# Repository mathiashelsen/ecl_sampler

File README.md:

ecl_sampler
===========

A sampling plugin driven by ECL logic

The idea is that a diode bridge can be pulsed on for a very short time (~50ps) through the use of 
an avalanche transtistor (and possibly step recovery diode.) 

The use of ECL enables a digitally controllable delay line to vary the position of the sample point to the trigger point.

Copyright 2014 by Mathias Helsen, MIT License.

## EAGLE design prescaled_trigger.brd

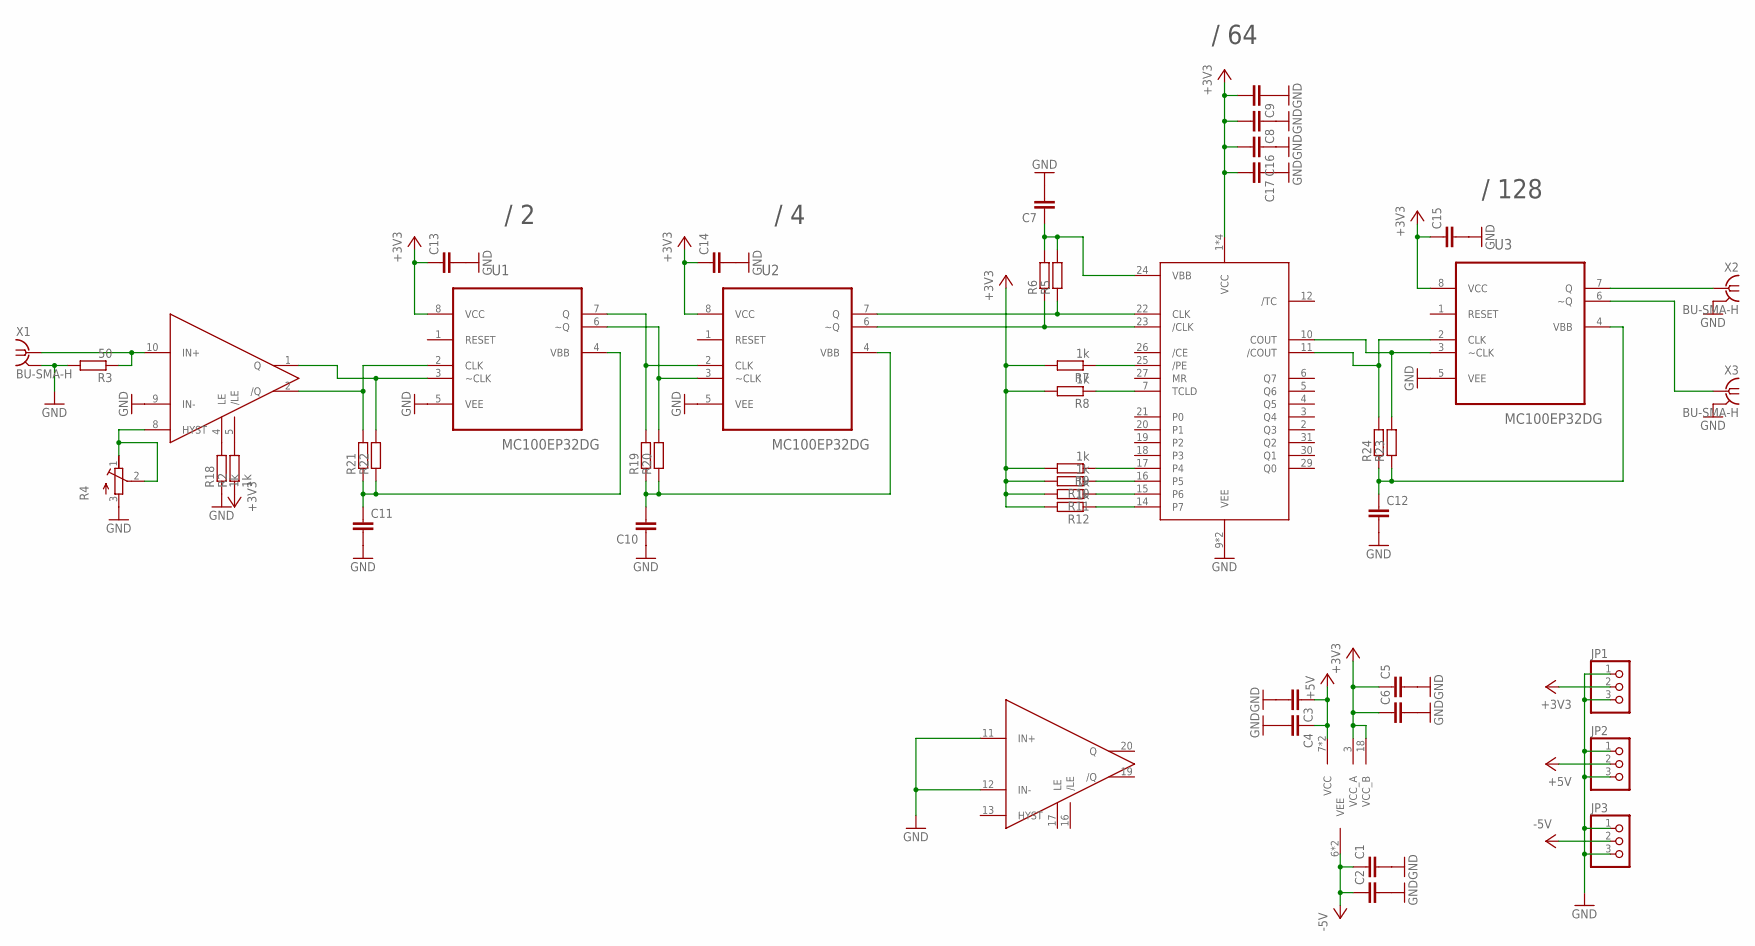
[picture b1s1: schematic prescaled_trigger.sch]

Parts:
C1, C2, C3, C4, C5, C6, C7, C8, C9, C10, C11, C12, C13, C14, C15, C16, C17: C-EUC0805; C0805
JP1, JP2, JP3: PINHD-1X3; 1X03
R2, R7, R8, R9, R10, R11, R12, R18: 1k; M0805
R3: 50; M0805
R4: R-TRIMMT18; RTRIMT18
R5, R6, R19, R20, R21, R22, R23, R24: R-EU_M1206; M1206
U1, U2, U3: MC100EP32DG; SOIC127P600X175-8N
U$1: MAX9601; SSOP20DB
U$2: MC100EP016; QFP80P900X900X160-32N
X1, X2, X3: BU-SMA-H

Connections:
+3V3: C5.1, C6.1, C8.2, C9.2, C13.1, C14.1, C15.1, C16.2, C17.2, JP1.2, R2.1, R7.2, R8.2, R9.2, R10.2, R11.2, R12.2, U1.8 (VCC), U2.8 (VCC), U3.8 (VCC), U$1.3 (VCC_A), U$1.18 (VCC_B), U$2.1 (VCC), U$2.8 (VCC), U$2.13 (VCC), U$2.32 (VCC)
+5V: C3.1, C4.1, JP2.2, U$1.7 (VCC), U$1.14 (VCC)
-5V: C1.1, C2.1, JP3.2, U$1.6 (VEE), U$1.15 (VEE)
/CLKIN: R6.1, U2.6 (~Q), U$2.23 (/CLK)
CLKIN: R5.1, U2.7 (Q), U$2.22 (CLK)
GND: C1.2, C2.2, C3.2, C4.2, C5.2, C6.2, C7.2, C8.1, C9.1, C10.1, C11.2, C12.2, C13.2, C14.2, C15.2, C16.1, C17.1, JP1.1, JP1.3, JP2.1, JP2.3, JP3.1, JP3.3, R3.2, R4.3 (E), R18.1, U1.5 (VEE), U2.5 (VEE), U3.5 (VEE), U$1.9 (IN-), U$1.11 (IN+), U$1.12 (IN-), U$2.9 (VEE), U$2.28 (VEE), X1.2, X1.3 (2), X1.4 (2), X1.5 (2), X2.2, X2.3 (2), X2.4 (2), X2.5 (2), X3.2, X3.3 (2), X3.4 (2), X3.5 (2)
unnamed: R2.2, U$1.5 (/LE)
unnamed: R11.1, U$2.15 (P6)
unnamed: R4.1 (A), R4.2 (S), U$1.8 (HYST)
unnamed: R10.1, U$2.16 (P5)
unnamed: R9.1, U$2.17 (P4)
unnamed: R12.1, U$2.14 (P7)
unnamed: R8.1, U$2.7 (TCLD)
unnamed: R7.1, U$2.25 (/PE)
unnamed: R18.2, U$1.4 (LE)
unnamed: C11.1, R21.1, R22.1, U1.4 (VBB)
unnamed: R21.2, U1.2 (CLK), U$1.2 (/Q)
unnamed: R22.2, U1.3 (~CLK), U$1.1 (Q)
unnamed: C10.2, R19.1, R20.1, U2.4 (VBB)
unnamed: R19.2, U1.7 (Q), U2.2 (CLK)
unnamed: R20.2, U1.6 (~Q), U2.3 (~CLK)
unnamed: U3.7 (Q), X2.1
unnamed: U3.6 (~Q), X3.1
unnamed: C12.1, R23.1, R24.1, U3.4 (VBB)
unnamed: R24.2, U3.2 (CLK), U$2.11 (/COUT)
unnamed: R23.2, U3.3 (~CLK), U$2.10 (COUT)
RFIN: R3.1, U$1.10 (IN+), X1.1
VBB: C7.1, R5.2, R6.2, U$2.24 (VBB)

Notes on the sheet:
/ 2
/ 4
/ 64
/ 128

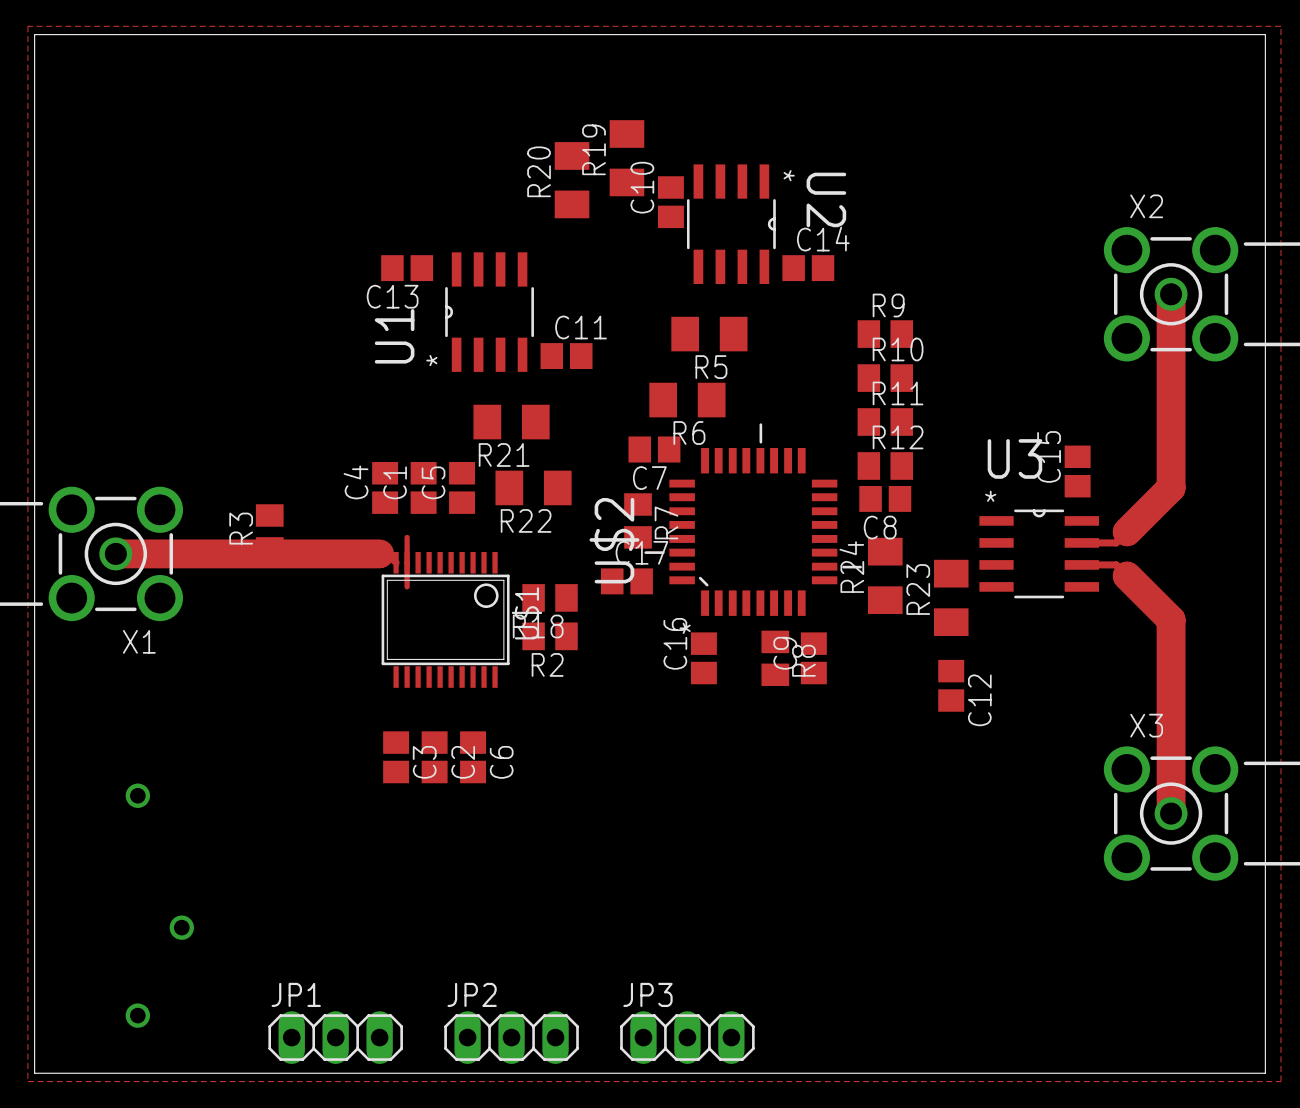
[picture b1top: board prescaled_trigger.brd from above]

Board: 2 copper layers, 71.1 x 60.0 mm, 46 parts (1 on the bottom side), 28 nets.

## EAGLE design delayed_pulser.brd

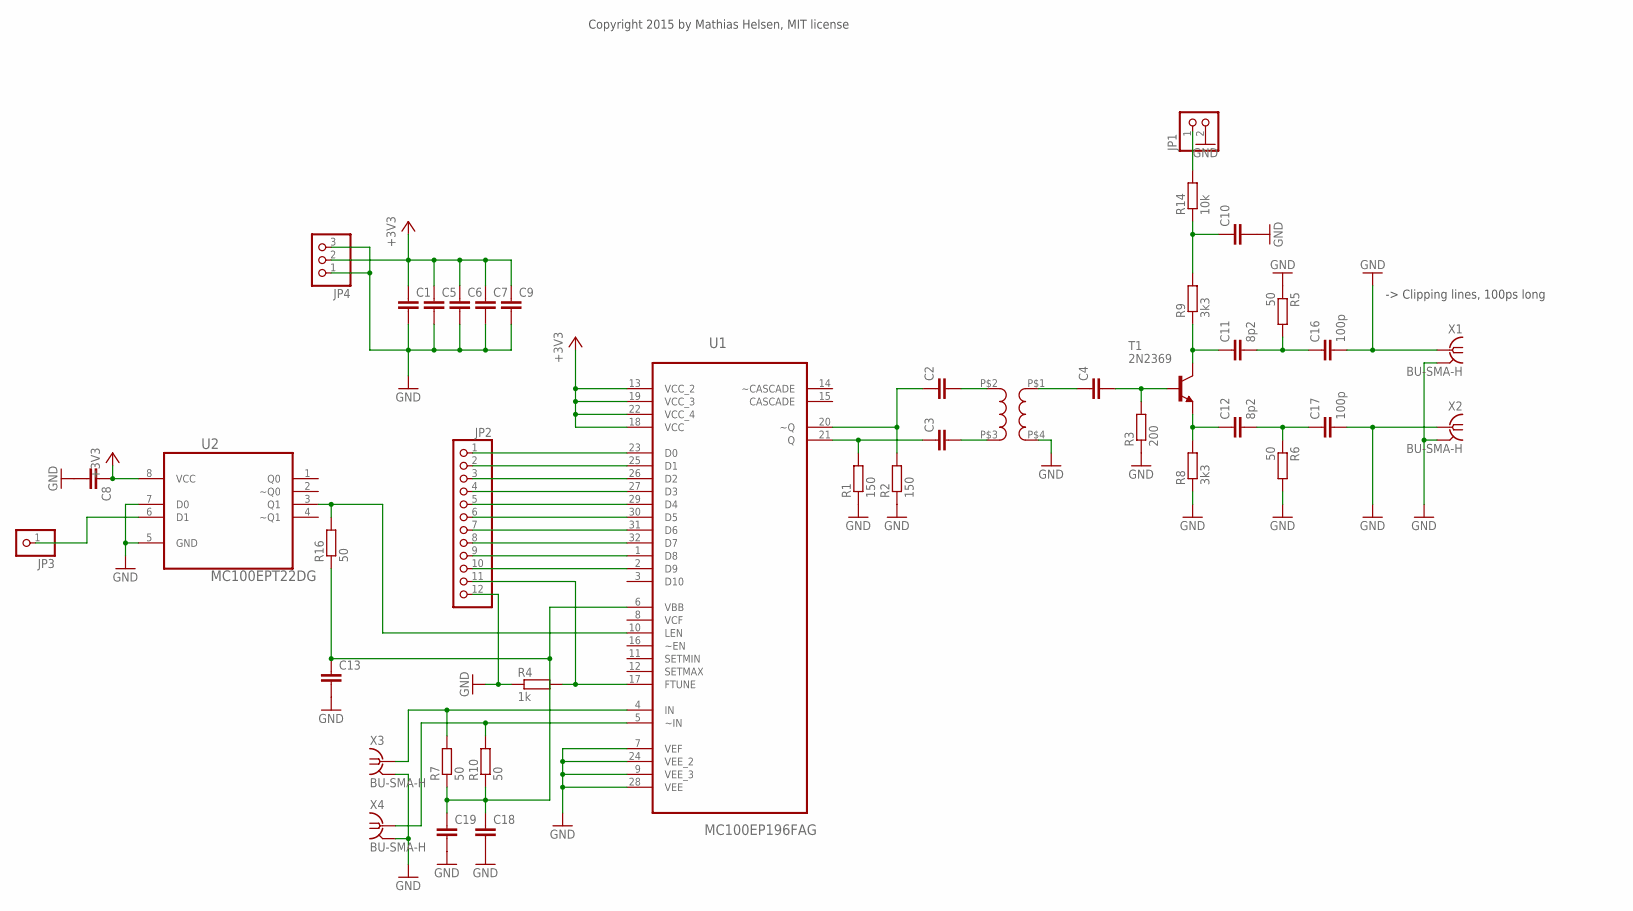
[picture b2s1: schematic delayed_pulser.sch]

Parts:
C1, C2, C3, C4, C5, C6, C7, C8, C10, C13, C18, C19: C-EUC0805; C0805
C9: C-EUC1206; C1206
C11, C12: 8p2; C0603
C16, C17: 100p; C0603
JP1: PINHD-1X2; 1X02
JP2: PINHD-1X12; 1X12
JP3: PINHD-1X1; 1X01
JP4: PINHD-1X3; 1X03
R1, R2: 150; R0805
R3: 200; R0805
R4: 1k; R0805
R5, R6: 50; R0603
R7, R10, R16: 50; R0805
R8, R9: 3k3; R0805
R14: 10k; R0805
T1: 2N2369; TO18
U1: MC100EP196FAG; QFP80P900X900X160-32N
U2: MC100EPT22DG; SOIC127P600X175-8N
U$1: JA4220; T
X1, X2, X3, X4: BU-SMA-H

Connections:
+3V3: C1.1, C5.1, C6.1, C7.1, C8.1, C9.1, JP4.2, U1.13 (VCC_2), U1.18 (VCC), U1.19 (VCC_3), U1.22 (VCC_4), U2.8 (VCC)
GND: C1.2, C5.2, C6.2, C7.2, C8.2, C9.2, C10.2, C13.2, C16.2, C17.2, C18.2, C19.2, JP1.2, JP2.12, JP4.1, JP4.3, R1.1, R2.1, R3.1, R4.1, R5.1, R6.2, R8.1, U1.7 (VEF), U1.9 (VEE_3), U1.24 (VEE_2), U1.28 (VEE), U2.5 (GND), U2.7 (D0), U$1.P$4, X1.1, X1.2, X1.3 (2), X1.4 (2), X1.5 (2), X2.1, X2.2, X2.3 (2), X2.4 (2), X2.5 (2), X3.2, X3.3 (2), X3.4 (2), X3.5 (2), X4.2, X4.3 (2), X4.4 (2), X4.5 (2)
unnamed: JP2.1, U1.23 (D0)
unnamed: C3.1, R1.2, U1.21 (Q)
unnamed: C2.1, R2.2, U1.20 (~Q)
unnamed: C2.2, U$1.P$2
unnamed: C3.2, U$1.P$3
unnamed: C4.1, U$1.P$1
unnamed: C4.2, R3.2, T1.2 (B)
unnamed: JP2.2, U1.25 (D1)
unnamed: JP2.11, R4.2, U1.17 (FTUNE)
unnamed: JP2.3, U1.26 (D2)
unnamed: C11.1, R9.1, T1.3 (C)
unnamed: C12.1, R8.2, T1.1 (E)
unnamed: JP2.4, U1.27 (D3)
unnamed: JP2.5, U1.29 (D4)
unnamed: JP2.6, U1.30 (D5)
unnamed: JP2.7, U1.31 (D6)
unnamed: JP2.8, U1.32 (D7)
unnamed: C10.1, R9.2, R14.1
unnamed: JP2.9, U1.1 (D8)
unnamed: JP2.10, U1.2 (D9)
unnamed: JP1.1, R14.2
unnamed: C11.2, C16.1, R5.2
unnamed: C12.2, C17.1, R6.1
unnamed: R10.2, U1.5 (~IN), X4.1
unnamed: R7.2, U1.4 (IN), X3.1
unnamed: R16.2, U1.10 (LEN), U2.3 (Q1)
unnamed: JP3.1, U2.6 (D1)
VBB: C13.1, C18.1, C19.1, R7.1, R10.1, R16.1, U1.6 (VBB)

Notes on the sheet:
Copyright 2015 by Mathias Helsen, MIT license
-> Clipping lines, 100ps long

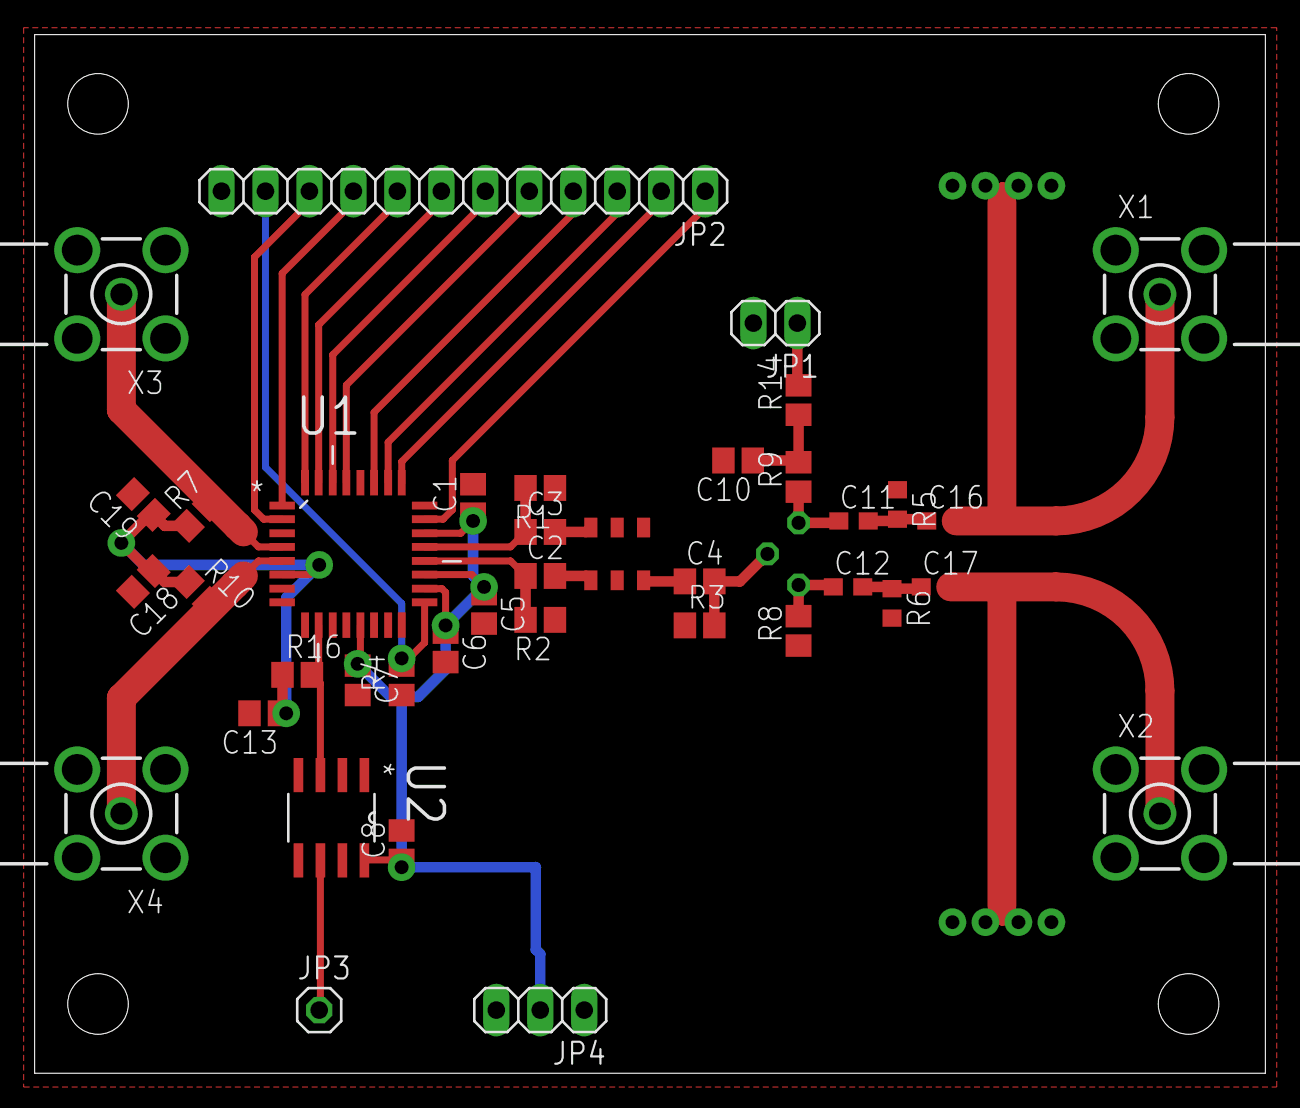
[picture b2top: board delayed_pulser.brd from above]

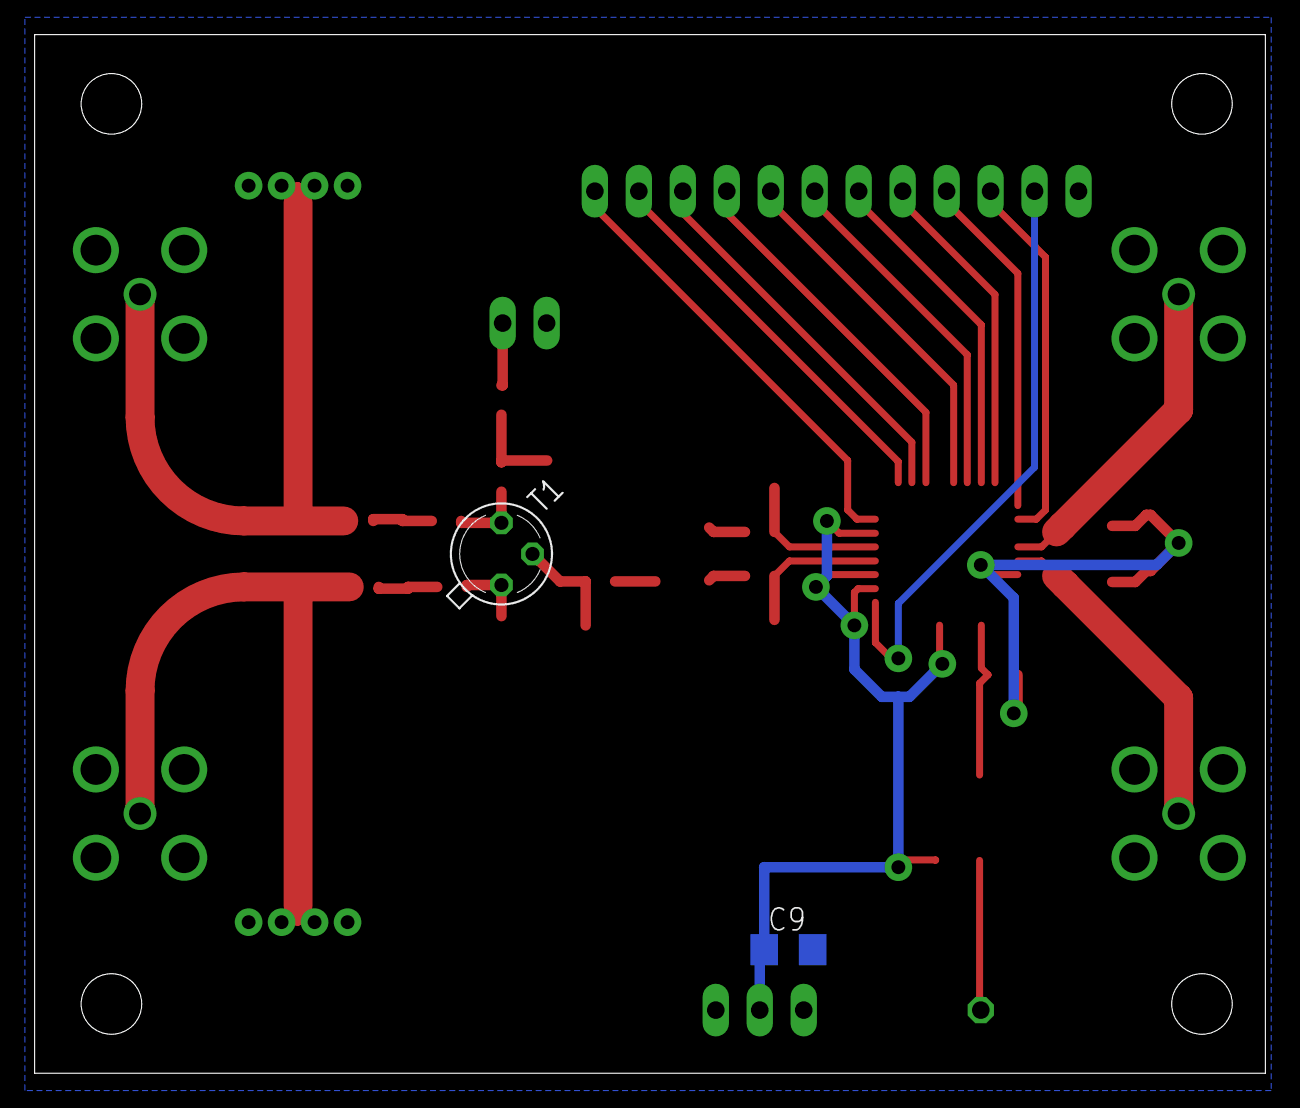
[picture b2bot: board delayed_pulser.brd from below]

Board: 2 copper layers, 71.1 x 60.0 mm, 41 parts (2 on the bottom side), 30 nets.

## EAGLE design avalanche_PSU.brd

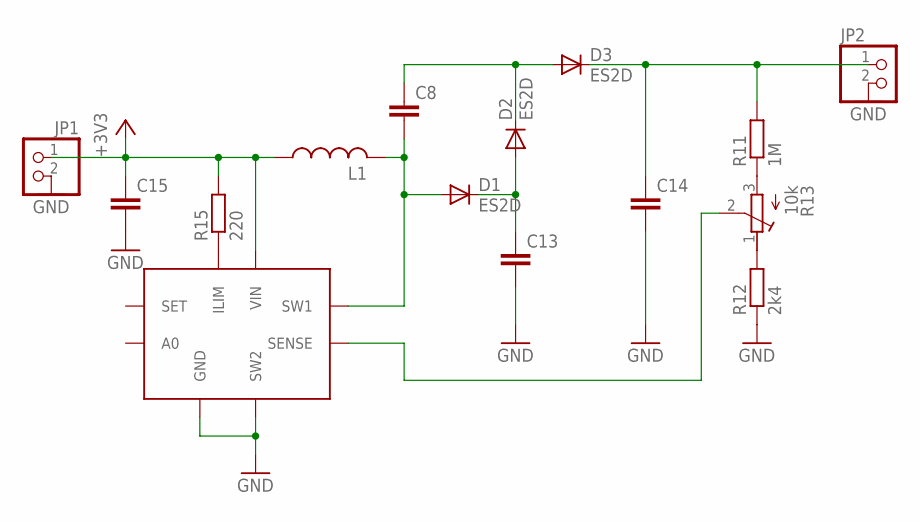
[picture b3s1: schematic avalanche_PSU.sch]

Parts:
C8, C13, C14: C-EUC0805K; C0805K
C15: C-EUC1206; C1206
D1, D2, D3: ES2D; SMB
JP1, JP2: PINHD-1X2; 1X02
L1: L-US; SRR1280
R11: 1M; M0805
R12: 2k4; M0805
R13: 10k; RTRIMT18
R15: 220; M0805
U$3: LT1073; DIL08

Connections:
+3V3: C15.1, JP1.1, L1.P$1 (1), R15.2, U$3.2 (VIN)
GND: C13.2, C14.2, C15.2, JP1.2, JP2.2, R12.1, U$3.4 (SW2), U$3.5 (GND)
unnamed: C13.1, D1.C, D2.A
unnamed: C8.1, D2.C, D3.A
unnamed: C14.1, D3.C, JP2.1, R11.2
unnamed: C8.2, D1.A, L1.P$2 (2), U$3.3 (SW1)
unnamed: R12.2, R13.1 (A)
unnamed: R11.1, R13.3 (E)
unnamed: R13.2 (S), U$3.8 (SENSE)
unnamed: R15.1, U$3.1 (ILIM)

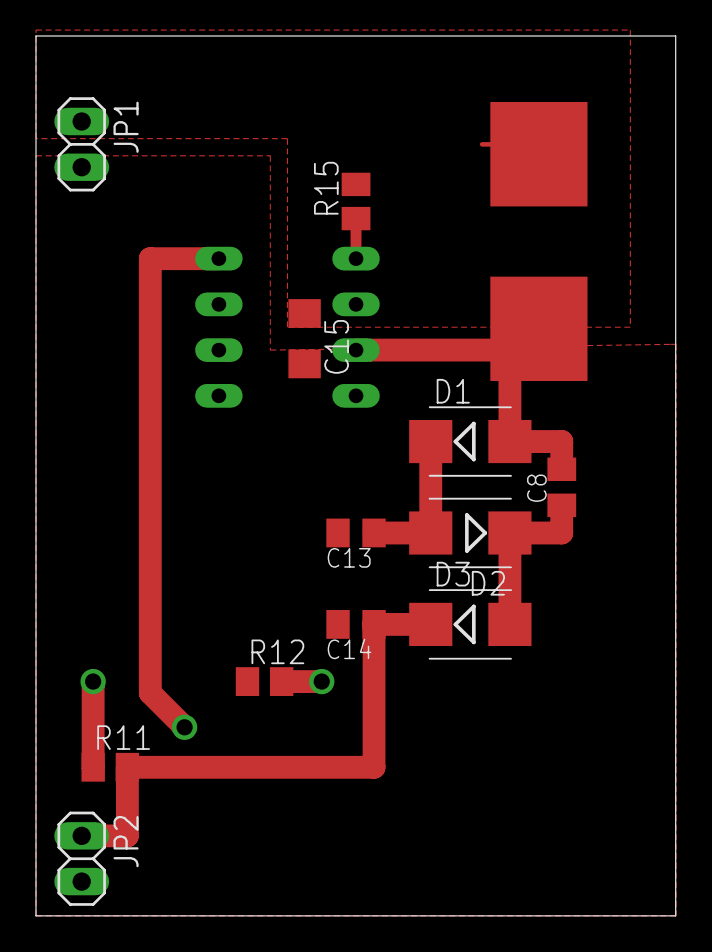
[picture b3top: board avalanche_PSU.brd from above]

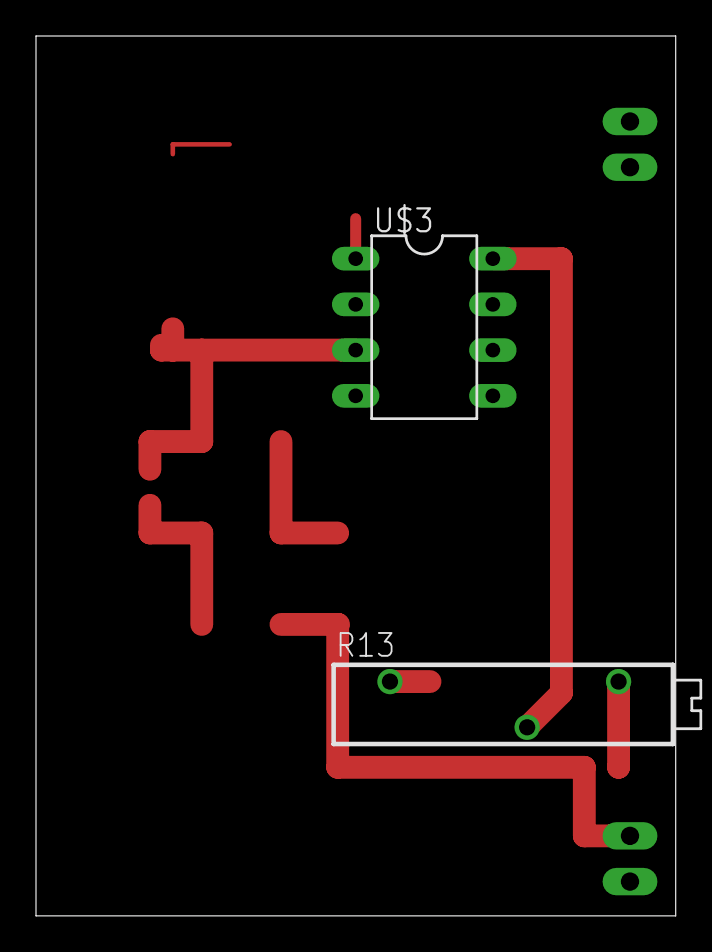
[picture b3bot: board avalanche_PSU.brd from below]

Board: 2 copper layers, 35.5 x 48.9 mm, 15 parts (2 on the bottom side), 10 nets.

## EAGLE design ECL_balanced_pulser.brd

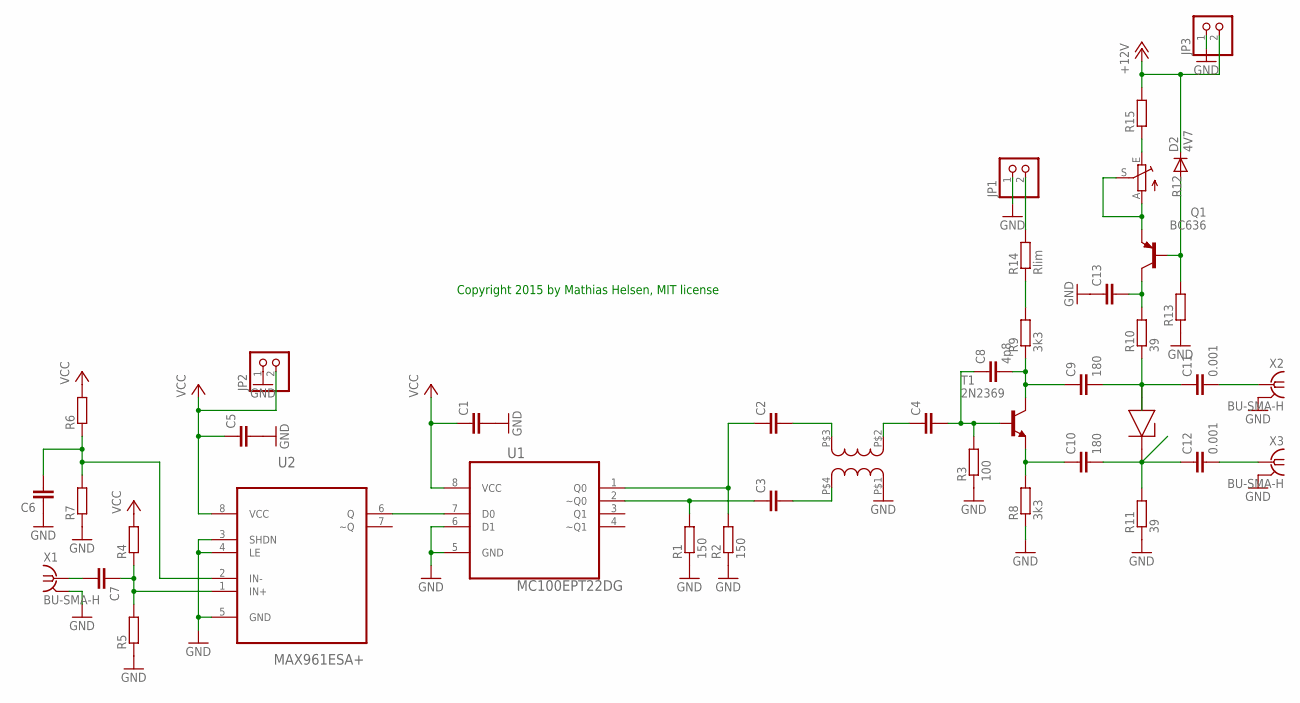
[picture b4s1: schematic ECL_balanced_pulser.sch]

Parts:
C1, C2, C3, C4, C5, C6, C7, C13: C-EUC0805; C0805
C8: 4p8; C0805
C9, C10: 180; C0805
C11, C12: 0.001; C0805
D2: 4V7; DO35-7
JP1, JP2, JP3: PINHD-1X2; 1X02
Q1: BC636; TO92-BCE
R1, R2: 150; R0805
R3: 100; R0805
R4, R5, R6, R7: R-EU_M0805; M0805
R8, R9: 3k3; R0805
R10, R11: 39; R0805
R12: TRIM_EU-SP19L; SP19L
R13, R15: R-EU_R0805; R0805
R14: Rlim; R0805
T1: 2N2369; TO18
U1: MC100EPT22DG; SOIC127P600X175-8N
U2: MAX961ESA+; SOIC127P600X175-8N
U$1: JA4220; T
U$2: 2D524A
X1, X2, X3: BU-SMA-H

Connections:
+12V: D2.C, JP3.2, R15.2
GND: C1.2, C5.2, C6.1, C13.1, JP1.1, JP2.1, JP3.1, R1.1, R2.1, R3.1, R5.1, R7.1, R8.1, R11.1, R13.1, U1.5 (GND), U1.6 (D1), U2.3 (SHDN), U2.4 (LE), U2.5 (GND), U$1.P$1, X1.2, X1.3 (2), X1.4 (2), X1.5 (2), X2.2, X2.3 (2), X2.4 (2), X2.5 (2), X3.2, X3.3 (2), X3.4 (2), X3.5 (2)
unnamed: U1.7 (D0), U2.6 (Q)
unnamed: C3.1, R1.2, U1.2 (~Q0)
unnamed: C2.1, R2.2, U1.1 (Q0)
unnamed: C2.2, U$1.P$3
unnamed: C3.2, U$1.P$4
unnamed: C4.1, U$1.P$2
unnamed: C4.2, C8.1, R3.2, T1.2 (B)
unnamed: C7.2, X1.1
unnamed: C7.1, R4.1, R5.2, U2.1 (IN+)
unnamed: C6.2, R6.1, R7.2, U2.2 (IN-)
unnamed: C8.2, C9.1, R9.1, T1.3 (C)
unnamed: C10.1, R8.2, T1.1 (E)
unnamed: JP1.2, R14.2
unnamed: C9.2, C11.1, R10.1, U$2.ANODE
unnamed: C11.2, X2.1
unnamed: C10.2, C12.1, R11.2, U$2.CATHODE
unnamed: C12.2, X3.1
unnamed: C13.2, Q1.C, R10.2
unnamed: R9.2, R14.1
unnamed: Q1.E, R12.A, R12.S
unnamed: D2.A, Q1.B, R13.2
unnamed: R12.E, R15.1
VCC: C1.1, C5.1, JP2.2, R4.2, R6.2, U1.8 (VCC), U2.8 (VCC)

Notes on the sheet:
Copyright 2015 by Mathias Helsen, MIT license

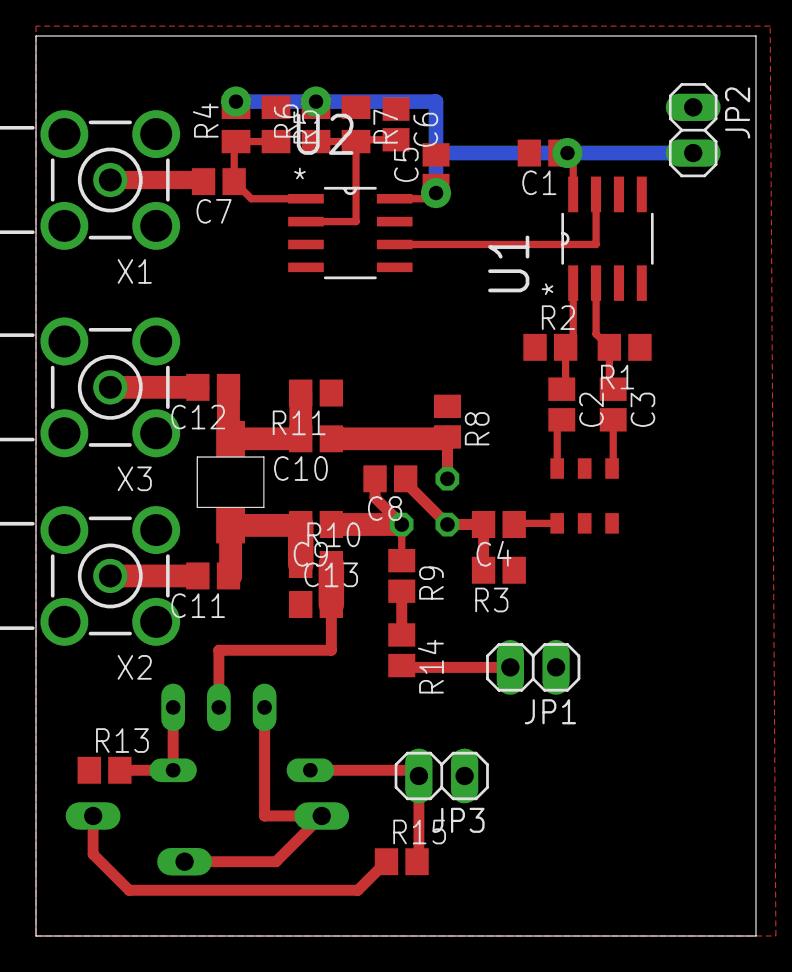
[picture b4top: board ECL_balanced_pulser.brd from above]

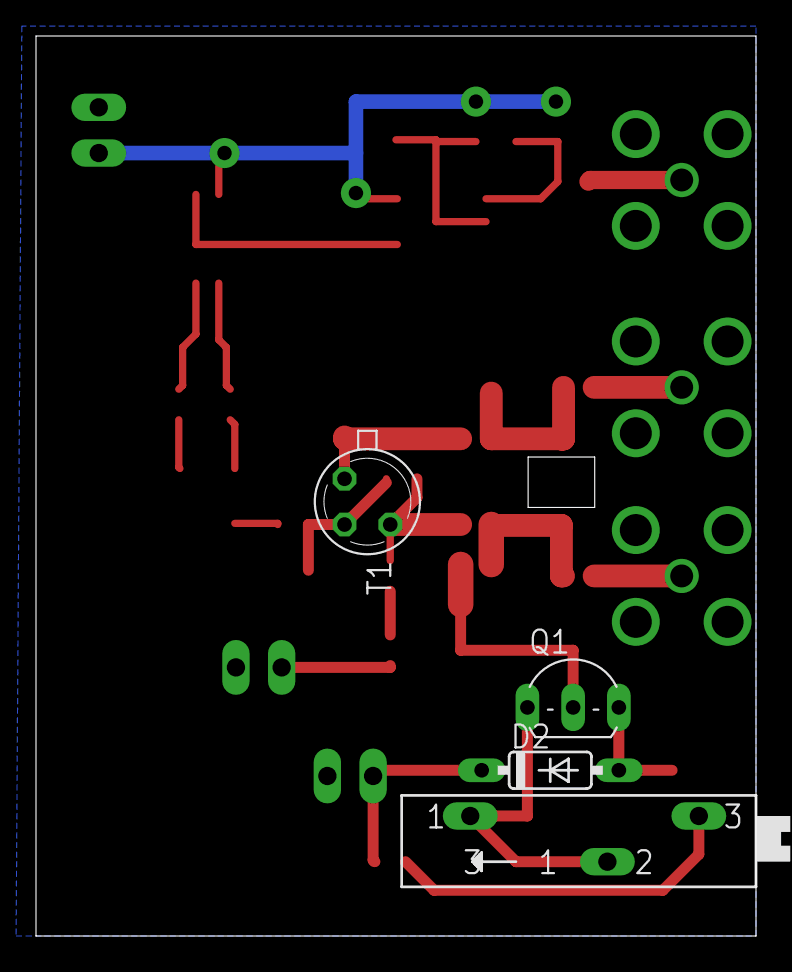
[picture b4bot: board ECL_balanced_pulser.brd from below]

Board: 2 copper layers, 40.0 x 50.0 mm, 41 parts (4 on the bottom side), 25 nets.

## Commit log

2014-04-25 update figure
2014-04-25 added a small copyright note
2014-04-26 custom footprint for 2D524A SRD
2014-04-29 added delayed pulse generator, only avalanche transistor for now
2014-04-30 added HV supply
2014-04-30 added comment
2014-05-02 finished artwork
2014-05-04 added high voltage PSU
2014-05-04 added pngs from schematics
2014-05-04 altered artwork
2014-05-14 added prescaled trigger, Work In Progress
2014-05-14 added my favorite libraries!
2014-05-15 almost finished prescaled trigger
2014-05-15 tracking board layout
